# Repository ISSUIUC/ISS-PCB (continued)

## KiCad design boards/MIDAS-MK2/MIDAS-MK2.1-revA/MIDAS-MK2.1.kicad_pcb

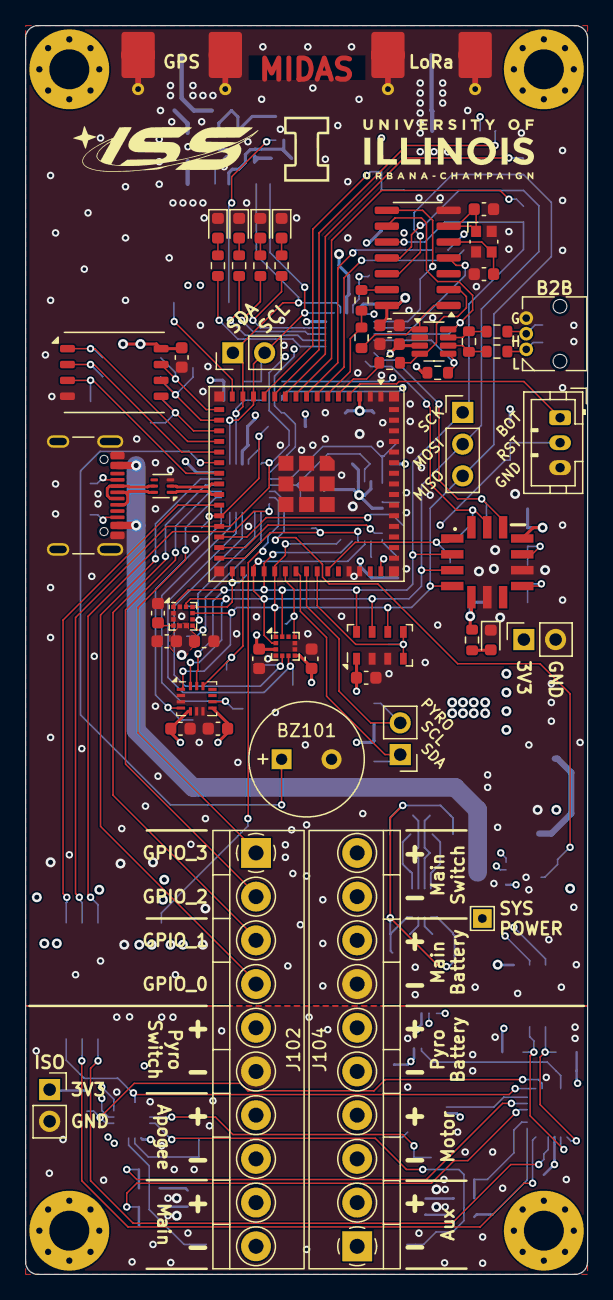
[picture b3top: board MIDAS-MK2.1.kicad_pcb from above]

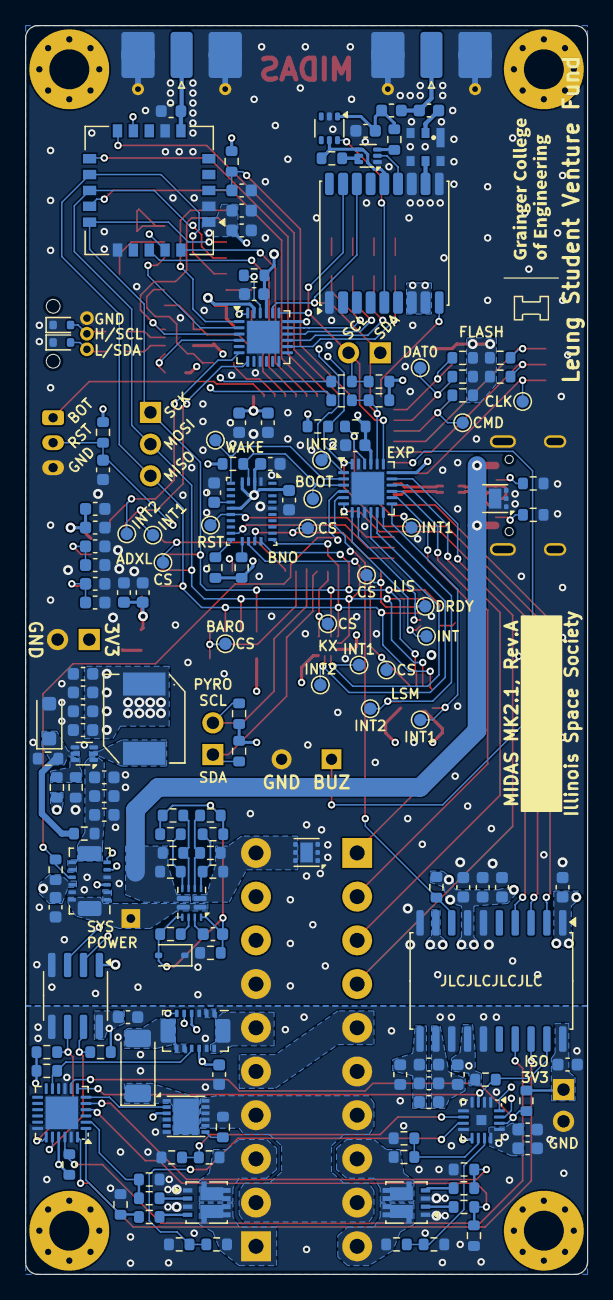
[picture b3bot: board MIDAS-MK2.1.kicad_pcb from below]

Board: 4 copper layers, 45.0 x 100.0 mm, 216 parts (159 on the bottom side), 154 nets.

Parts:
BZ101: AT-0927-TT-6-R; Buzzer_AT-0927-TT-6-R
C101, C102, C103, C107, C108, C109, C110, C201, C208, C209, C210, C211, C212, C301, C401, C502, C504, C506, C507, C508, C510, C511, C512, C513, C514, C515, C517, C518, C519: 0.1uF; C_0603_1608Metric
C104, C105: 22pF; C_0603_1608Metric
C106, C304, C305, C306, C307: 22uF; C_0603_1608Metric
C111, C204, C205, C308, C501, C503, C505, C509, C516: 1uF; C_0603_1608Metric
C202, C203, C402, C405: 10nF; C_0603_1608Metric
C206, C207, C302, C303, C404: 10uF; C_0603_1608Metric
C403: 47pF; C_0603_1608Metric
D101, D102: ESD321; D_SOD-523
D103, D303: RED LED; LED_0603_1608Metric
D104: ORANGE LED; LED_0603_1608Metric
D105: GREEN LED; LED_0603_1608Metric
D106: BLUE LED; LED_0603_1608Metric
D201: RSX501LAM20; D_SOD-128
D301: BZT52H-A5V1-QX; D_SOD-123F
D302: BAS416; D_SOD-323
FB201, FB202: BLM18SG331TN1D; L_0603_1608Metric
FL401: B3913; Qualcomm_SMD-6
H101, H102, H103, H104: M3; MountingHole_3.2mm_M3_Pad_Via
J101: USB4105-GF-A; USB_C_Receptacle_GCT_USB4105-xx-A_16P_TopMnt_Horizontal
J102: Left; Molex_Terminal-Block_393570010_1x10_P3.5mm
J103: Conn_01x03; Molex_Micro-Lock_2200980371_1x03_P1.25mm_Horizontal
J104: Right; Molex_Terminal-Block_393570010_1x10_P3.5mm
J105, J106: Conn_01x02; PinHeader_1x02_P2.54mm_Vertical
J107: Conn_01x03; PinHeader_1x03_P2.54mm_Vertical
J108: Conn_01x03; JST_PH_B3B-PH-K_1x03_P2.00mm_Vertical
J201, J302: Conn_01x02; PinSocket_1x02_P2.54mm_Vertical
J301: TestPoint; TestPoint_THTPad_1.5x1.5mm_Drill0.7mm
J401, J402: SMA; SMA_Molex_73251-2120_EdgeMount_Horizontal
L301: 2.2uH; L_TDK_SPM6530
L401: 27nH; L_0603_1608Metric
L402: 330nH; L_0603_1608Metric
Q201, Q202: Si7232DN; Vishay_PowerPAK_1212-8_Dual
Q401: Si1016X; SOT-563
R101, R104, R105, R106, R220, R222: 4.7k; R_0603_1608Metric
R102, R103, R107, R108, R114, R201, R221, R223, R224, R501: 10k; R_0603_1608Metric
R109, R110, R111, R112, R113: 50k; R_0603_1608Metric
R115, R116, R117, R118, R119, R120, R121, R312: 0; R_0603_1608Metric
R122: 120; R_0603_1608Metric
R123, R124: 5.1k; R_0603_1608Metric
R125, R303: 20k; R_0603_1608Metric
R126, R127, R128, R129, R315: 470; R_0603_1608Metric
R202, R206, R207, R214, R215: 1k; R_0603_1608Metric
R203, R301, R302, R305, R308, R310: 5k; R_0603_1608Metric
R204, R205, R212, R213: 3.3k; R_0603_1608Metric
R208, R209, R216, R217, R401, R403: 100k; R_0603_1608Metric
R210, R211, R218, R219, R306, R311: 30k; R_0603_1608Metric
R304: 27k; R_0603_1608Metric
R307: 33k; R_0603_1608Metric
R309: 69.8k; R_0603_1608Metric
R313: 135k; R_0603_1608Metric
R314: 21.5k; R_0603_1608Metric
R402: 10; R_0603_1608Metric
R502, R503: 2.2k; R_0603_1608Metric
TP101, TP102, TP103, TP104, TP105, TP106, TP107, TP108, TP109, TP110, TP111, TP112, TP113, TP114, TP115, TP116, TP117, TP118, TP119, TP120, TP121, TP122: TestPoint_Small; TestPoint_Pad_D1.0mm
U101, U201: INA745x; VQFN-REL0014B
U102, U103, U205: TCAL9539-Q1; WQFN-24-1EP_4x4mm_P0.5mm_EP2.6x2.6mm
U104: ESP32-S3-MINI-1U; ESP32-S2-MINI-1U
U105: MCP2518FDT-xSL; SOIC-14_3.9x8.7mm_P1.27mm
U106: ZDSD64GLGEAG-R; LGA-8_8x6.2mm_P1.27mm
U107: TCAN337G; SOT-23-8
U108: ECMF02-2AMX6; ST_UQFN-6L_1.5x1.7mm_P0.5mm
U202: NPC45560-H; DFN-12-1EP_3x3mm_P0.5mm_EP2.05x2.86mm
U203: ISOW7742; SOIC-20W_7.5x12.8mm_P1.27mm
U204: ISO1640BDR; SOIC-8_3.9x4.9mm_P1.27mm
U206: ADS122C04IRTE; Texas_RTE0016D_WQFN-16-1EP_3x3mm_P0.5mm_EP0.8x0.8mm
U301, U302: TVS1800DRV; WSON-6-1EP_2x2mm_P0.65mm_EP1x1.6mm
U303: TI_TPS566242; SOT-563
U304: TPS2121; Texas_VQFN-HR-12_2x2.5mm_P0.5mm
U401: E22-400MM22S
U402: NC7WZ07; SOT-363_SC-70-6
U403: MAX-M10S; ublox_MAX
U501: KX134-1211; LGA-12_2x2mm_P0.5mm
U502: ADXL355; Analog_LGA_14-7.4x7.4mm
U503: LSM6DSLTR; Bosch_LGA-14_3x2.5mm_P0.5mm
U504: BNO086; LGA-28_5.2x3.8mm_P0.5mm
U505: LIS3MDL; LGA-12_2x2mm_P0.5mm
U506: MS5611-01BA03; LGA-8_3x5mm_P1.25mm
Y101: 40MHz; Crystal_SMD_Abracon_ABM10-4Pin_2.5x2.0mm

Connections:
+3V3: C101.2, C102.1, C103.1, C106.2, C107.2, C108.2, C109.2, C110.2, C202.1, C204.1, C206.1, C209.1, C304.1, C305.1, C306.1, C307.1, C404.1, C405.1, C501.2, C502.2, C503.2, C504.1, C506.1, C508.1, C511.1, C512.1, C514.1, C515.1, C516.2, C517.2, C519.1, J302.1, L301.1, R101.2, R102.2, R103.2, R104.2, R105.2, R106.2, R107.1, R108.2, R109.2, R110.2, R111.2, R112.2, R113.2, R114.1, R125.2, R203.1, R313.2, R315.1, R401.2, R501.2, R502.2, R503.2, U101.3 (A1), U101.11 (VS), U102.18 (A0), U102.21 (VCC), U103.18 (A0), U103.21 (VCC), U103.23 (A1), U104.3 (3V3), U105.14 (VDD), U106.8 (VDD), U107.3 (VCC), U203.1 (V_{IO}), U203.7 (EN_IO1), U203.9 (V_{DD}), U204.1 (VCC1), U401.1 (VCC), U403.7 (VCC_IO), U403.8 (VCC), U501.3 (IO_VDD), U501.7 (VDD), U502.5 (V_{DDIO}), U502.11 (V_{SUPPLY}), U503.5 (VDDIO), U503.8 (VDD), U504.3 (VDD), U504.5 (PS1), U504.10 (CLKSEL0), U504.28 (VDDIO), U505.5 (Vdd), U505.6 (Vdd_IO), U506.1 (VDD)
+3V3_ISO: C201.2, C208.1, C210.1, C211.1, C212.1, FB201.1, J201.1, R201.1, R220.2, R221.2, R222.2, R223.2, R224.2, U201.4 (A0), U201.11 (VS), U202.3 (VCC), U203.14 (EN_IO2), U203.20 (V_{ISOIN}), U204.8 (VCC2), U205.21 (VCC), U206.9 (REFP), U206.12 (AVDD), U206.13 (DVDD)
/ADC_RESET: U104.25 (IO21), U203.2 (INA)
/ADXL355_CS: TP107.1, U104.40 (RXD0), U502.1 (~CS/SCL)
/ADXL355_INT1: TP109.1, U103.7 (P06), U502.13 (INT2)
/ADXL355_INT2: TP108.1, U103.6 (P05), U502.12 (INT1)
/AUX_GPIO_0: J102.4, U102.17
/AUX_GPIO_1: J102.3, U102.16
/AUX_GPIO_2: J102.2, U102.15
/AUX_GPIO_3: J102.1, U102.14
/BNO086_BOOT: R501.1, TP106.1, U102.3 (P02), U504.4 (BOOTN)
/BNO086_CS: TP103.1, U104.30 (IO48), U504.18 (H_CSN)
/BNO086_INT: U104.29 (IO34), U504.14 (H_INTN)
/BNO086_RESET: TP104.1, U104.28 (IO33), U504.11 (NRST)
/BNO086_WAKE: TP105.1, U102.2 (P01), U504.6 (PS0/WAKE)
/BOOT_SW: J108.1, U104.4 (IO0)
/BUZZER: BZ101.1 (-), U104.21 (IO17)
/CANH: R117.1, R122.1, U107.7 (CANH)
/CANL: R115.1, R122.2, U107.6 (CANL)
/CAN_1: R119.1, R120.1, U104.6 (IO2)
/CAN_2: R121.1, U104.5 (IO1)
/CAN_FAULT: R114.2, U103.4 (P03), U107.5 (FAULT)
/CAN_NCS: R119.2, U105.13 (NCS)
/CAN_NINT: U103.2 (P01), U105.4 (~INT)
/CAN_NINT1: U103.1 (P00), U105.8 (~INT1/GPIO1)
/CAN_RXD: R121.2, U105.2 (RXCAN), U107.4 (RXD)
/CAN_SLNT: U103.3 (P02), U105.9 (~INT0/GPIO0/XSTBY), U107.8 (S)
/CAN_TXD: R120.2, U105.1 (TXCAN), U107.1 (TXD)
/D+: J101.A6 (D+), J101.B6 (D+), U108.6 (D+_out)
/D-: J101.A7 (D-), J101.B7 (D-), U108.5 (D-_out)
/E22_BUSY: U104.10 (IO6), U401.11 (BUSY)
/E22_CS: U104.9 (IO5), U401.14 (NSS)
/E22_DIO1: U104.8 (IO4), U401.20 (DIO1)
/E22_DIO3: U104.7 (IO3), U401.18 (DIO3)
/E22_RESET: C401.1, R401.1, U104.12 (IO8), U401.3 (NRST)
/E22_RXEN: U104.11 (IO7), U401.10 (RXEN)
/EXP_INT0: U102.6 (P05), U203.4 (OUTC)
/EXP_INT1: R102.1, TP101.1, U102.22 (~INT), U104.26 (IO26)
/EXP_INT2: R103.1, TP102.1, U102.1 (P00), U103.22 (~INT)
/EXP_RESET: R108.1, U102.24 (~RESET), U103.24 (~RESET), U104.27 (IO47), U203.3 (INB)
/FLASH_CLK: TP121.1, U104.22 (IO18), U106.3 (CLK)
/FLASH_CMD: R113.1, TP120.1, U104.18 (IO14), U106.5 (CMD)
/FLASH_DAT0: R109.1, TP122.1, U104.17 (IO13), U106.6 (DAT0)
/FLASH_DAT1: R110.1, U104.16 (IO12), U106.7 (DAT1)
/FLASH_DAT2: R111.1, U104.19 (IO15), U106.1 (DAT2)
/FLASH_DAT3: R112.1, U104.20 (IO16), U106.2 (DAT3)
/I2C_SCL: J105.2, R104.1, R118.1, U102.19 (SCL), U103.19 (SCL), U104.13 (IO9), U403.17 (SCL)
/I2C_SDA: J105.1, R101.1, R116.1, U102.20 (SDA), U103.20 (SDA), U104.14 (IO10), U403.16 (SDA)
/INA_ALERT: R107.2, U101.10 (ALERT), U102.4 (P03)
/ISO_FLT: R203.2, U102.5 (P04), U203.8 (EN/FLT)
/KX134_CS: TP110.1, U104.36 (IO40), U501.10 (nCS)
/KX134_INT1: TP112.1, U102.10, U501.5 (INT1)
/KX134_INT2: TP111.1, U102.11, U501.6 (INT2)
/LED_BLUE: R129.1, U103.14
/LED_GREEN: R128.1, U103.15
/LED_ORANGE: R127.1, U103.16
/LED_RED: R126.1, U103.17
/LIS3MDL_CS: TP113.1, U104.31 (IO35), U505.10 (CS)
/LIS3MDL_DRDY: TP114.1, U102.8 (P07), U505.8 (DRDY)
/LIS3MDL_INT: TP115.1, U102.7 (P06), U505.7 (INT)
/LSM6DSLTR_INT1: TP117.1, U102.13, U503.4 (INT1)
/LSM6DSLTR_INT2: TP118.1, U102.12, U503.9 (INT2)
/LSM6DSL_CS: TP116.1, U104.32 (IO36), U503.12 (CS)
/MAX_RESET: U104.15 (IO11), U403.9 (~RESET)
/MS5611_CS: TP119.1, U104.39 (TXD0), U506.4 (CSB), U506.5 (CSB)
/PYRO_A: J102.8, Q201.5 (D2), R208.2
/PYRO_B: J102.10, Q201.6 (D1), R216.2
/PYRO_C: J104.3, Q202.6 (D1), R209.2
/PYRO_D: J104.1, Q202.5 (D2), R217.2
/PYRO_SCL: J106.2, R106.1, U101.6 (SCL), U104.38 (IO42), U204.3 (SCL1)
/PYRO_SDA: J106.1, R105.1, U101.5 (SDA), U104.37 (IO41), U204.2 (SDA1)
/PYRO_SW: J102.5, J104.5
/Power/MUX_CP2: R307.2, R308.1, U304.3 (CP2)
/Pyro Circuitry/ADC_DRDY: R224.1, U205.8 (P07), U206.14 (DRDY)
/Pyro Circuitry/ADC_RST_ISO: R223.1, U203.19 (OUTA), U205.7 (P06), U206.3 (RESET)
/Pyro Circuitry/EXP_INT_ISO: R221.1, U203.17 (INC), U205.22 (~INT)
/Pyro Circuitry/EXP_RST_ISO: U203.18 (OUTB), U205.24 (~RESET)
/Pyro Circuitry/FIRE_A: R204.1, R206.1, U205.5 (P04)
/Pyro Circuitry/FIRE_B: R212.1, R214.1, U205.4 (P03)
/Pyro Circuitry/FIRE_C: R205.1, R207.1, U205.2 (P01)
/Pyro Circuitry/FIRE_D: R213.1, R215.1, U205.1 (P00)
/Pyro Circuitry/GND2: C203.2, C205.2, C207.2, FB202.2, U203.11 (GND2)
/Pyro Circuitry/INA_ALRT_ISO: R201.2, U201.10 (ALERT), U205.11
/Pyro Circuitry/ISO_SCL: R222.1, U201.6 (SCL), U204.6 (SCL2), U205.19 (SCL), U206.16 (SCL)
/Pyro Circuitry/ISO_SDA: R220.1, U201.5 (SDA), U204.7 (SDA2), U205.20 (SDA), U206.15 (SDA)
/Pyro Circuitry/PYRO_EN: U202.2 (EN), U205.6 (P05)
/Pyro Circuitry/SENSE_A: R208.1, R210.2, U206.10 (AIN1)
/Pyro Circuitry/SENSE_B: R216.1, R218.2, U206.11 (AIN0)
/Pyro Circuitry/SENSE_C: R209.1, R211.2, U206.6 (AIN3)
/Pyro Circuitry/SENSE_D: R217.1, R219.2, U206.7 (AIN2)
/Pyro Circuitry/V_ISOOUT: C203.1, C205.1, C207.1, FB201.2, U203.12 (V_{ISOOUT})
/Pyro Circuitry/V_PYRO_ZONE: D201.2 (A), U201.7 (IS-)
/RESET_SW: C111.1, J108.2, R125.1, U104.45 (EN)
/RF/MAX_INT: U402.6 (Y1), U403.5 (EXTINT)
/SPI_MISO: J107.3, U104.35 (IO39), U105.12 (SDO), U401.12 (MISO), U501.1 (SDO/ADDR), U502.4 (MISO/ASEL), U503.1 (SDO/SA0), U504.20 (H_SDA/H_MISO/TX), U505.9 (SDO/SA1), U506.6 (SDO)
/SPI_MOSI: J107.2, U104.33 (IO37), U105.11 (SDI), U401.13 (MOSI), U501.2 (SDI/SDA), U502.3 (MOSI/SDA), U503.14 (SDA), U504.17 (H_SA0_MOSI), U505.11 (SDA/SDI/SDO), U506.7 (SDI/SDA)
/SPI_SCK: J107.1, U104.34 (IO38), U105.10 (SCK), U401.15 (SCK), U501.12 (SCLK/SCL), U502.2 (SCLK/V_{SSIO}), U503.13 (SCL), U504.19 (H_SCL/SCK/RX), U505.1 (SCL/SPC), U506.8 (SCLK)
/SYS_POWER: J301.1, U101.13 (VBUS), U101.14 (IS+), U304.1 (OUT), U304.8 (OUT)
/USB_D+: U104.24 (IO20), U108.1 (D+_in)
/USB_D-: U104.23 (IO19), U108.2 (D-_in)
/USB_POWER: J101.A4 (VBUS), J101.A9 (VBUS), J101.B4 (VBUS), J101.B9 (VBUS), R301.1, R304.1, U301.4 (IN), U301.5 (IN), U301.6 (IN), U304.7 (IN1)
/VBAT: J104.10, R307.1, R309.1, U302.4 (IN), U302.5 (IN), U302.6 (IN), U304.2 (IN2)
/VBAT_PYRO: J104.6, U201.13 (VBUS), U201.14 (IS+)
/VREG_IN: C301.1, C302.1, C303.1, R303.1, U101.7 (IS-), U303.1 (VIN)
/V_PYRO: J102.7, J102.9, J104.2, J104.4, R202.1, U202.8 (VOUT), U202.9 (VOUT), U202.10 (VOUT), U202.11 (VOUT), U202.12 (VOUT)
GND: BZ101.2 (+), C101.1, C102.2, C103.2, C104.1, C105.2, C106.1, C107.1, C108.1, C109.1, C110.1, C111.2, C202.2, C204.2, C206.2, C209.2, C301.2, C302.2, C303.2, C304.2, C305.2, C306.2, C307.2, C401.2, C402.2, C404.2, C405.2, C501.1, C502.1, C503.1, C504.2, C505.1, C506.2, C507.2, C508.2, C509.1, C510.2, C511.2, C512.2, C513.2, C514.2, C515.2, C516.1, C517.1, C518.1, C519.2, D101.1 (A1), D102.1 (A1), D103.1 (K), D104.1 (K), D105.1 (K), D106.1 (K), D301.2 (A), D302.1 (K), D303.1 (K), FL401.1 (GND), FL401.3 (GND), FL401.4 (GND), FL401.6 (GND), J101.A1 (GND), J101.A12 (GND), J101.B1 (GND), J101.B12 (GND), J101.S1 (SHIELD), J103.3, J104.7, J108.3, J302.2, J401.2 (Ext), J402.2 (Ext), L402.2, Q401.1 (S1), R123.2, R124.2, R306.2, R311.2, R312.2, U101.4 (A0), U101.12 (GND), U102.9 (GND), U102.23 (A1), U102.25 (GND), U103.9 (GND), U103.25 (GND), U104.1 (GND), U104.2 (GND), U104.42 (GND), U104.43 (GND), U104.46 (GND), U104.47 (GND), U104.48 (GND), U104.49 (GND), U104.50 (GND), U104.51 (GND), U104.52 (GND), U104.53 (GND), U104.54 (GND), U104.55 (GND), U104.56 (GND), U104.57 (GND), U104.58 (GND), U104.59 (GND), U104.60 (GND), U104.61 (GND), U104.62 (GND), U104.63 (GND), U104.64 (GND), U104.65 (GND), U105.7 (VSS), U106.4 (GND), U107.2 (GND), U108.3 (GND), U203.6 (GNDIO), U203.10 (GND1), U204.4 (GND1), U301.1 (GND), U301.2 (GND), U301.3 (GND), U301.7 (GND), U302.1 (GND), U302.2 (GND), U302.3 (GND), U302.7 (GND), U303.3 (GND), U303.4 (AGND), U401.2 (GND), U401.7 (GND), U401.16 (GND), U402.2 (GND), U403.1 (GND), U403.10 (GND), U403.12 (GND), U501.4 (TRIG), U501.8 (GND), U501.9 (GND), U502.6 (V_{SSIO}), U502.9 (VSS), U503.2 (SDx), U503.3 (SCx), U503.6 (GND), U503.7 (GND), U504.2 (GND), U504.25 (GNDIO), U505.2 (Reserved), U505.3 (GND), U505.12 (Reserved), U506.2 (PS), U506.3 (GND), Y101.2, Y101.4
unnamed: D101.2 (A2), J103.1, R115.2, R116.2
unnamed: D102.2 (A2), J103.2, R117.2, R118.2
unnamed: D103.2 (A), R126.2
unnamed: D104.2 (A), R127.2
unnamed: D105.2 (A), R128.2
unnamed: D106.2 (A), R129.2
unnamed: D201.1 (K), U202.1 (VIN), U202.13 (VIN)
unnamed: D301.1 (K), R303.2, R306.1, U303.5 (EN)
unnamed: C308.1, D302.2 (A), R302.2, R305.2, R308.2, R310.2, R312.1, R314.1, U304.9 (ST), U304.12 (GND)
unnamed: D303.2 (A), R315.2
unnamed: C403.2, FL401.2 (IN)
unnamed: FL401.5 (OUT), U403.11 (RF_IN)
unnamed: J101.A5 (CC1), R123.1
unnamed: J101.B5 (CC2), R124.1
unnamed: J104.8, J104.9
unnamed: C403.1, J401.1 (In), L401.1
unnamed: J402.1 (In), L402.1, U401.6 (ANT)
unnamed: Q201.2 (G1), R214.2
unnamed: Q201.4 (G2), R206.2
unnamed: Q202.2 (G1), R207.2
unnamed: Q202.4 (G2), R215.2
unnamed: Q401.5 (G2), Q401.6 (D1), R403.1
unnamed: Q401.2 (G2), U403.13 (LNA_EN)
unnamed: Q401.3 (D2), R402.1
unnamed: Q401.4 (S2), R403.2, U402.5 (VCC), U403.14 (VCC_RF)
unnamed: U101.1 (SH+), U101.2 (IN+)
unnamed: U101.8 (SH-), U101.9 (IN-)
unnamed: C105.1, U105.6 (OSC1), Y101.1
unnamed: C104.2, U105.5 (OSC2), Y101.3
unnamed: U201.1 (SH+), U201.2 (IN+)
unnamed: U201.8 (SH-), U201.9 (IN-)
unnamed: R202.2, U202.7 (BLEED)
unnamed: R311.1, R313.1, U303.6 (FB)
unnamed: L301.2, U303.2 (SW)
unnamed: R314.2, U304.10 (ILM)
unnamed: R304.2, R305.1, U304.5 (OV1)
unnamed: R309.2, R310.1, U304.4 (OV2)
unnamed: R301.2, R302.1, U304.6 (PR1)
unnamed: C308.2, U304.11 (SS)
unnamed: U401.9 (TXEN), U401.19 (DIO2)
unnamed: C402.1, L401.2, R402.2, U402.1 (A1)
unnamed: C505.2, C507.1, U502.10 (V_{1P8ANA})
unnamed: C509.2, C510.1, U502.8 (V_{1P8DIG})
unnamed: C513.1, U504.9 (CAP)
unnamed: R503.1, U504.15 (ENV_SCL)
unnamed: R502.1, U504.16 (ENV_SDA)
unnamed: C518.2, U505.4 (C1)
PYRO_GND: C201.1, C208.2, C210.2, C211.2, C212.2, FB202.1, J102.6, J201.2, Q201.1 (S1), Q201.3 (S2), Q202.1 (S1), Q202.3 (S2), R204.2, R205.2, R210.1, R211.1, R212.2, R213.2, R218.1, R219.1, U201.3 (A1), U201.12 (GND), U202.4 (GND), U202.6 (PG), U203.13 (VSEL), U203.15 (GISOIN), U204.5 (GND2), U205.9 (GND), U205.18 (A0), U205.23 (A1), U205.25 (GND), U206.1 (A0), U206.2 (A1), U206.4 (DGND), U206.5 (AVSS), U206.8 (REFN), U206.17 (EP)
